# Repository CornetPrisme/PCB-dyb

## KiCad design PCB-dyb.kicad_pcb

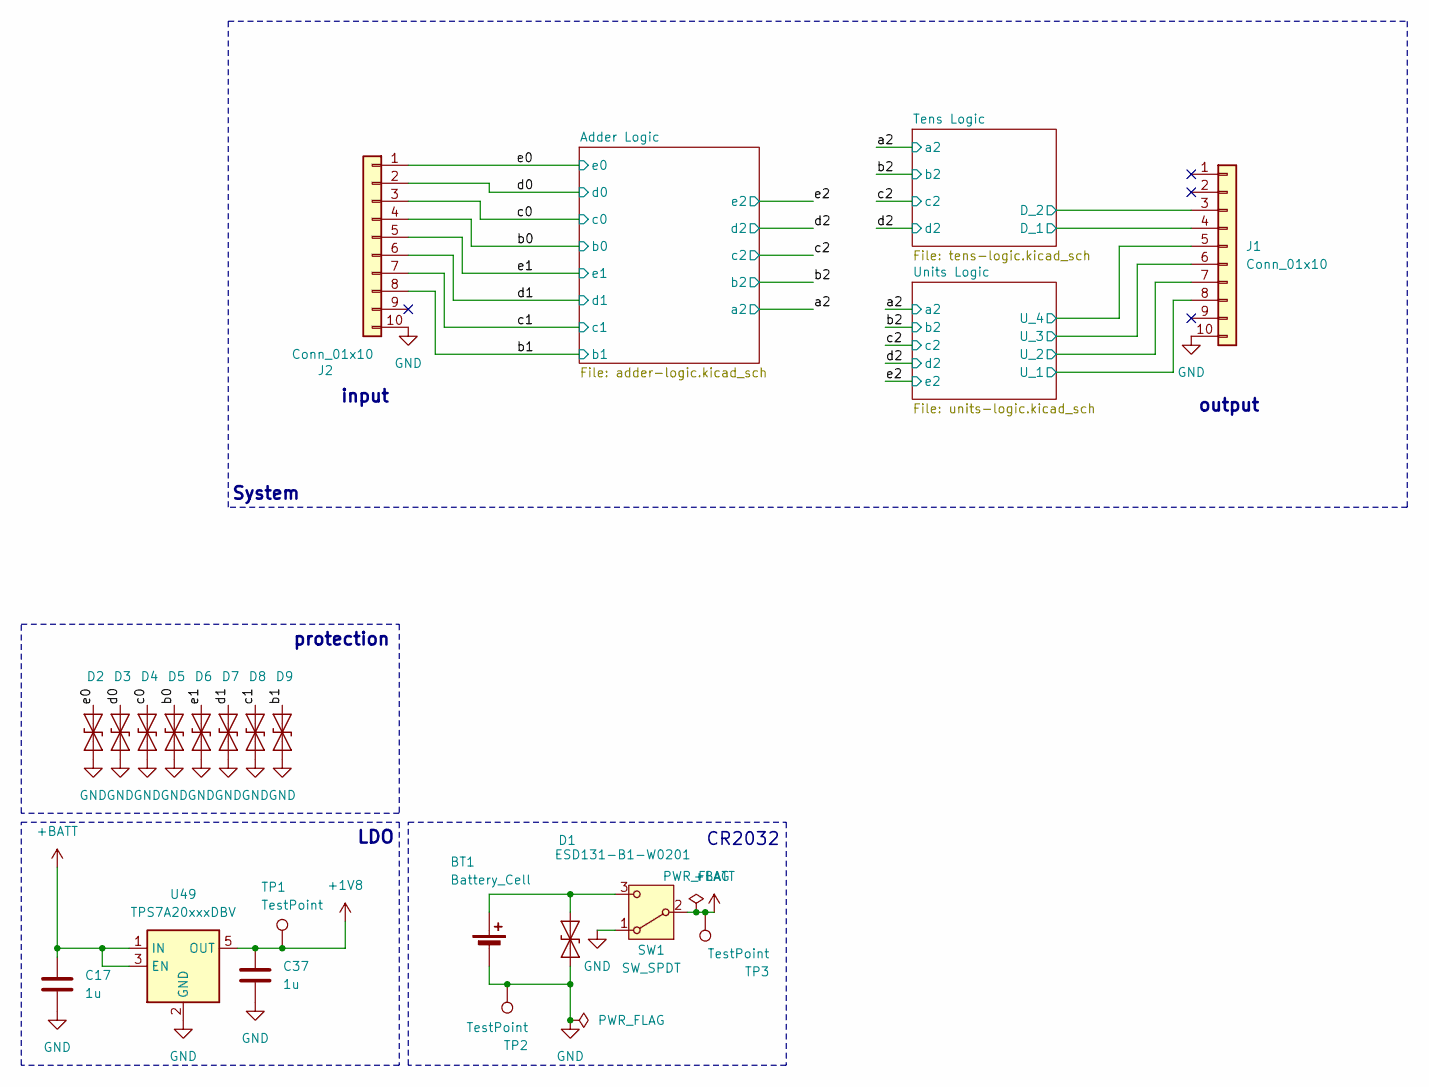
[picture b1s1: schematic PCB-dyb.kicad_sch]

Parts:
BT1: Battery_Cell; Manufacturer Part Number BS-08-B2AA016; JLCPCB Part # C964792
C17, C37: 1u; C_0603_1608Metric; Manufacturer Part Number CL10A105KO8NNNC; JLCPCB Part # C1592
D1, D2, D3, D4, D5, D6, D7, D8, D9: ESD131-B1-W0201; Infineon_SG-WLL-2-3_0.58x0.28_P0.36mm; Manufacturer Part Number TSD05CDYFR; JLCPCB Part # C20611048
J1, J2: Conn_01x10; PinHeader_1x10_P2.54mm_Vertical
SW1: SW_SPDT; SW_SPDT_Shouhan_MSK12C02; Manufacturer Part Number MSK12C02; JLCPCB Part # C431540
TP1, TP2, TP3: TestPoint
U49: TPS7A20xxxDBV; SOT-23-5; Manufacturer Part Number TPS7A2018PDBVR; JLCPCB Part # C963430

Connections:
+1V8: C37.1, TP1.1, U49.5 (OUT); also elsewhere on the board
+BATT: C17.1, SW1.2 (B), TP3.1, U49.1 (IN), U49.3 (EN)
/Tens Logic/D_1: J1.4; also elsewhere on the board
/Tens Logic/D_2: J1.3; also elsewhere on the board
/Units Logic/U_2: J1.7; also elsewhere on the board
/Units Logic/U_3: J1.6; also elsewhere on the board
/Units Logic/U_4: J1.5; also elsewhere on the board
/b0: D5.2 (A2), J2.4; also elsewhere on the board
/b1: D9.2 (A2), J2.8; also elsewhere on the board
/c0: D4.2 (A2), J2.3; also elsewhere on the board
/c1: D8.2 (A2), J2.7; also elsewhere on the board
/d0: D3.2 (A2), J2.2; also elsewhere on the board
/d1: D7.2 (A2), J2.6; also elsewhere on the board
/e0: D2.2 (A2), J2.1; also elsewhere on the board
/e1: D6.2 (A2), J2.5; also elsewhere on the board
/e2: J1.8; also elsewhere on the board
GND: BT1.2 (-), C17.2, C37.2, D1.1 (A1), D2.1 (A1), D3.1 (A1), D4.1 (A1), D5.1 (A1), D6.1 (A1), D7.1 (A1), D8.1 (A1), D9.1 (A1), J1.10, J2.10, SW1.1 (A), TP2.1, U49.2 (GND); also elsewhere on the board
unnamed: BT1.1 (+), D1.2 (A2), SW1.3 (C)

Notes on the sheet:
CR2032
System
output
protection
LDO
input

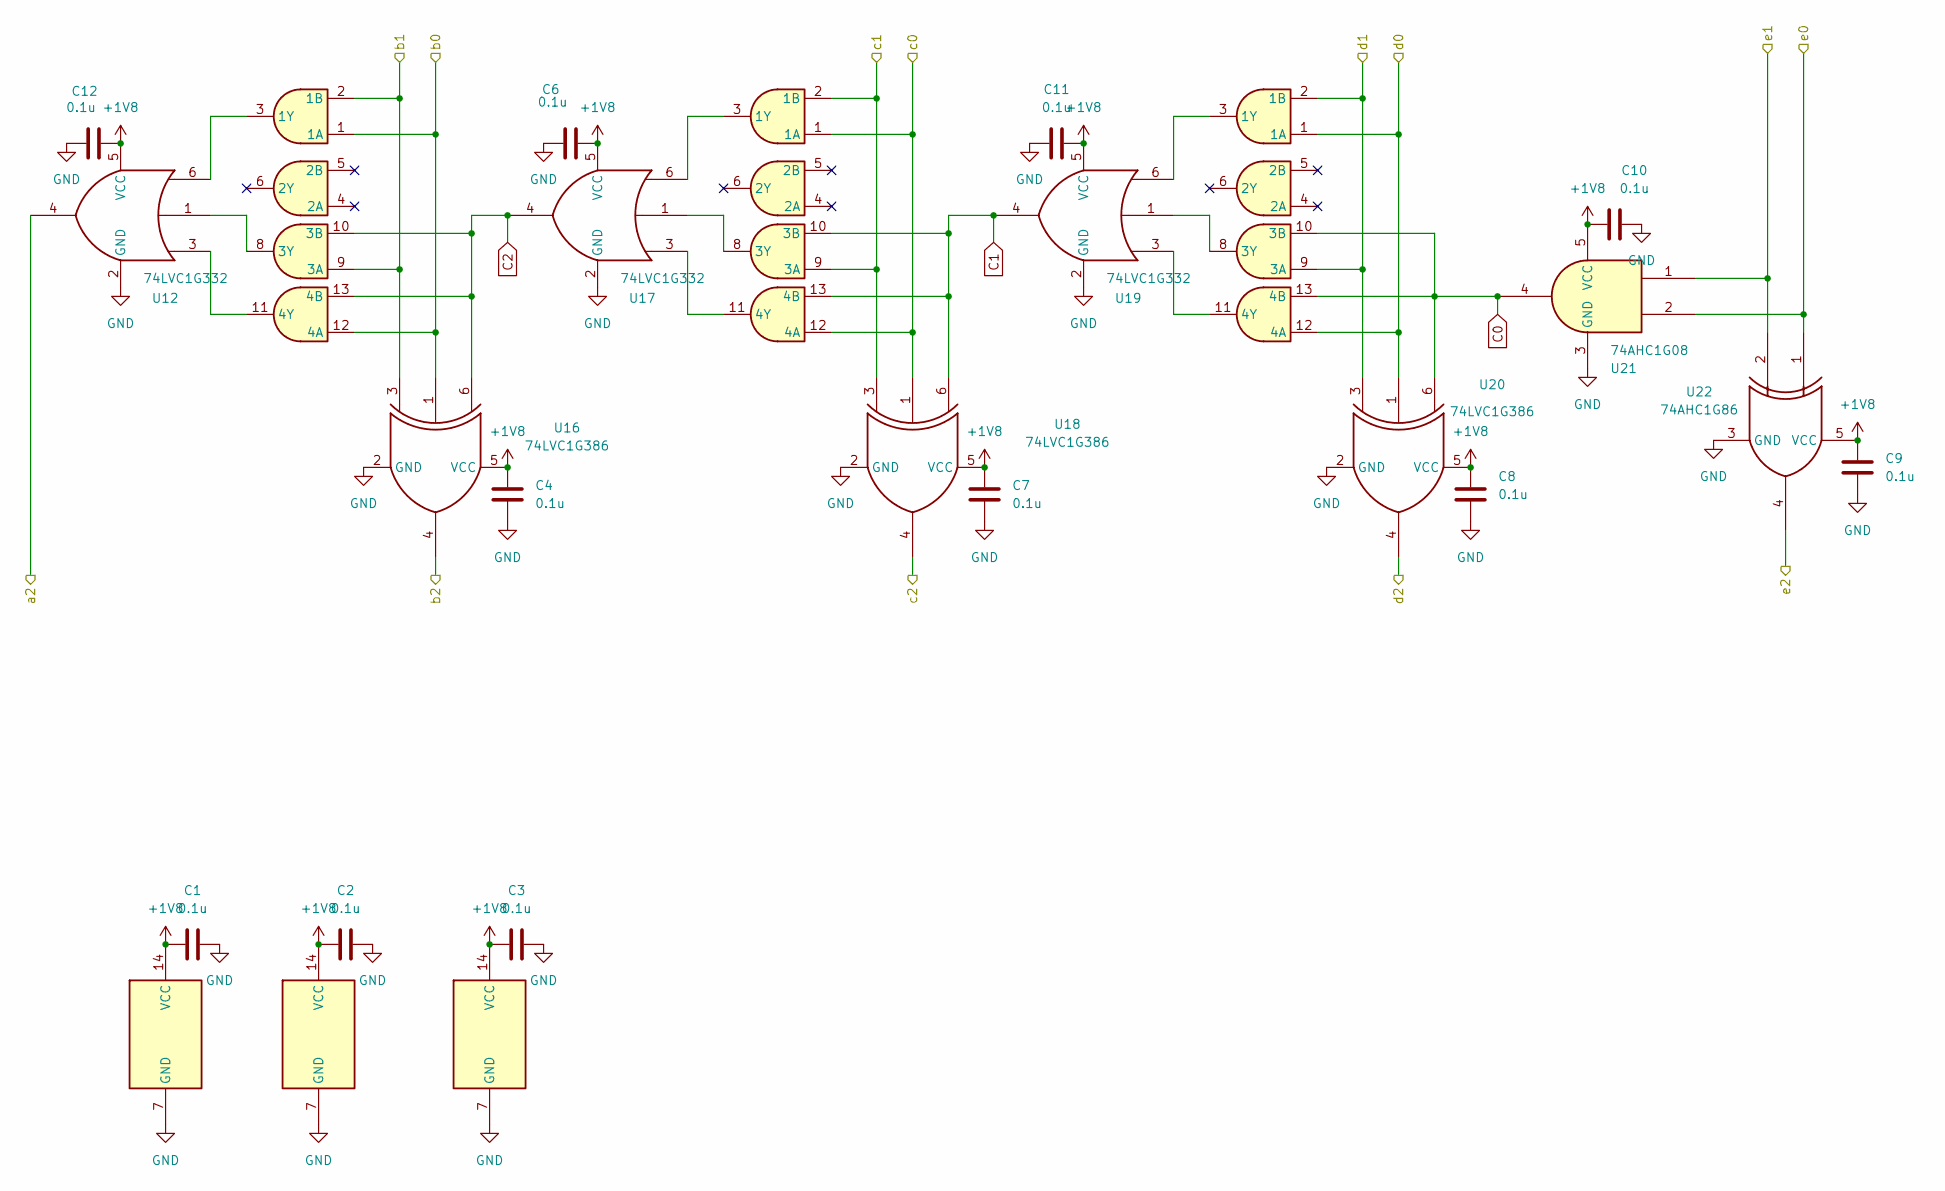
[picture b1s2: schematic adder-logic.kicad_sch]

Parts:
C1, C2, C3, C4, C6, C7, C8, C9, C10, C11, C12: 0.1u; C_0603_1608Metric; Manufacturer Part Number CL10B104KB8NNNC; JLCPCB Part # C1591
U12, U17, U19: 74LVC1G332; SOT-23-6; Manufacturer Part Number SN74LVC1G332DBVR; JLCPCB Part # C43368
U13, U14, U15: SOIC-14_3.9x8.7mm_P1.27mm; Manufacturer Part Number SN74ALVC08DR; JLCPCB Part # C2868761
U16, U18, U20: 74LVC1G386; Texas_R-PDSO-G6; Manufacturer Part Number SN74LVC1G386DCKR; JLCPCB Part # C2867271
U21: 74AHC1G08; SOT-353_SC-70-5; Manufacturer Part Number SN74AUC1G08DCKR; JLCPCB Part # C2863707
U22: 74AHC1G86; SOT-353_SC-70-5; Manufacturer Part Number SN74AUC1G86DCKR; JLCPCB Part # C2869047

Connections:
+1V8: C1.1, C2.1, C3.1, C4.2, C6.2, C7.1, C8.2, C9.2, C10.1, C11.1, C12.1, U12.5 (VCC), U13.14 (VCC), U14.14 (VCC), U15.14 (VCC), U16.5 (VCC), U17.5 (VCC), U18.5 (VCC), U19.5 (VCC), U20.5 (VCC), U21.5 (VCC), U22.5 (VCC); also elsewhere on the board
/a2: U12.4; also elsewhere on the board
/b0: U13.1 (1A), U13.12 (4A), U16.1; also elsewhere on the board
/b1: U13.2 (1B), U13.9 (3A), U16.3; also elsewhere on the board
/b2: U16.4; also elsewhere on the board
/c0: U14.1 (1A), U14.12 (4A), U18.1; also elsewhere on the board
/c1: U14.2 (1B), U14.9 (3A), U18.3; also elsewhere on the board
/c2: U18.4; also elsewhere on the board
/d0: U15.1 (1A), U15.12 (4A), U20.1; also elsewhere on the board
/d1: U15.2 (1B), U15.9 (3A), U20.3; also elsewhere on the board
/d2: U20.4; also elsewhere on the board
/e0: U21.2, U22.1; also elsewhere on the board
/e1: U21.1, U22.2; also elsewhere on the board
/e2: U22.4; also elsewhere on the board
C0: U15.10 (3B), U15.13 (4B), U20.6, U21.4
C1: U14.10 (3B), U14.13 (4B), U18.6, U19.4
C2: U13.10 (3B), U13.13 (4B), U16.6, U17.4
GND: C1.2, C2.2, C3.2, C4.1, C6.1, C7.2, C8.1, C9.1, C10.2, C11.2, C12.2, U12.2 (GND), U13.7 (GND), U14.7 (GND), U15.7 (GND), U16.2 (GND), U17.2 (GND), U18.2 (GND), U19.2 (GND), U20.2 (GND), U21.3 (GND), U22.3 (GND); also elsewhere on the board
unnamed: U12.6, U13.3 (1Y)
unnamed: U12.1, U13.8 (3Y)
unnamed: U12.3, U13.11 (4Y)
unnamed: U14.3 (1Y), U17.6
unnamed: U14.8 (3Y), U17.1
unnamed: U14.11 (4Y), U17.3
unnamed: U15.3 (1Y), U19.6
unnamed: U15.8 (3Y), U19.1
unnamed: U15.11 (4Y), U19.3

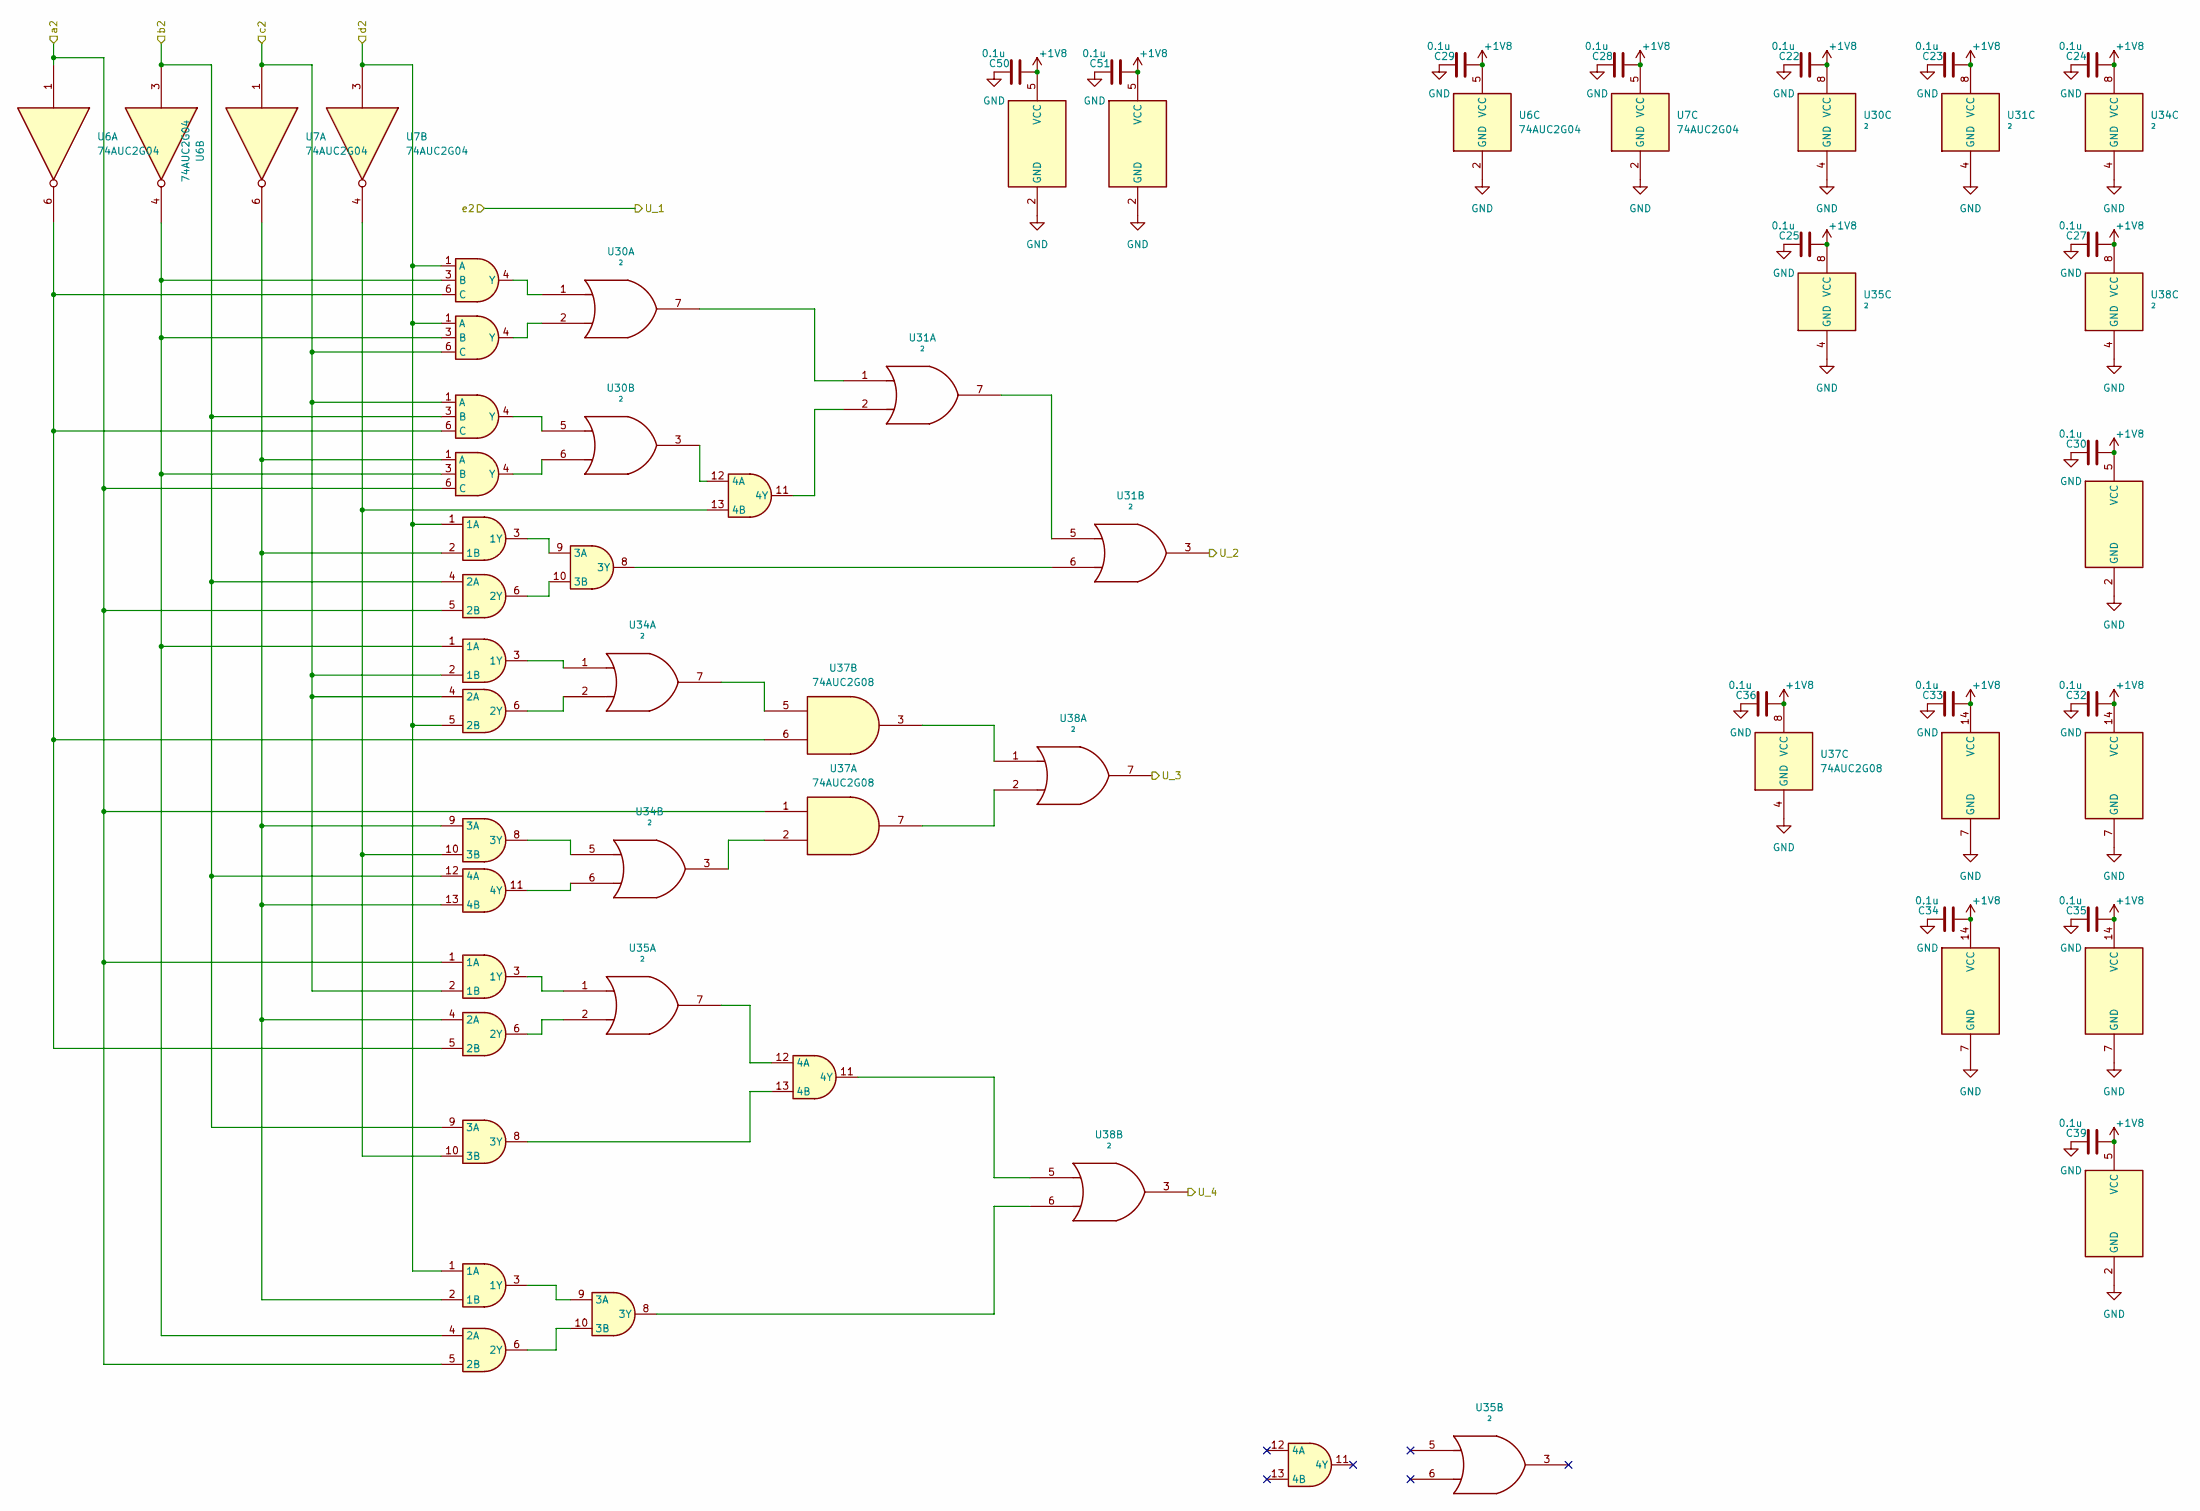
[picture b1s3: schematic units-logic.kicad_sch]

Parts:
C22, C23, C24, C25, C27, C28, C29, C30, C32, C33, C34, C35, C36, C39, C50, C51: 0.1u; C_0603_1608Metric; Manufacturer Part Number CL10B104KB8NNNC; JLCPCB Part # C1591
U6, U7: 74AUC2G04; Texas_R-PDSO-G6; Manufacturer Part Number SN74AUP2G14DCKR; JLCPCB Part # C139318
U9, U36, U39, U41: SOIC-14_3.9x8.7mm_P1.27mm; Manufacturer Part Number SN74ALVC08DR; JLCPCB Part # C2868761
U10, U11, U32, U33: SOT-23-6; Manufacturer Part Number SN74LVC1G11DBVR; JLCPCB Part # C22046
U30, U31, U34, U35, U38: ²; VSSOP-8_3x3mm_P0.65mm; Manufacturer Part Number SN74AUP2G32DCUR; JLCPCB Part # C2876519
U37: 74AUC2G08; Texas_DGN0008B_VSSOP-8-1EP_3x3mm_P0.65mm_EP2x3mm_Mask1.88x1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; Manufacturer Part Number SN74AUC2G08DCUR; JLCPCB Part # C2860154

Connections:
+1V8: C22.2, C23.2, C24.2, C25.2, C27.2, C28.2, C29.2, C30.2, C32.2, C33.2, C34.2, C35.2, C36.2, C39.2, C50.2, C51.2, U6.5 (VCC), U7.5 (VCC), U9.14 (VCC), U10.5 (VCC), U11.5 (VCC), U30.8 (VCC), U31.8 (VCC), U32.5 (VCC), U33.5 (VCC), U34.8 (VCC), U35.8 (VCC), U36.14 (VCC), U37.8 (VCC), U38.8 (VCC), U39.14 (VCC), U41.14 (VCC); also elsewhere on the board
/Units Logic/U_2: U31.3; also elsewhere on the board
/Units Logic/U_3: U38.7; also elsewhere on the board
/Units Logic/U_4: U38.3; also elsewhere on the board
/a2: U6.1, U9.5 (2B), U33.6 (C), U37.1, U39.1 (1A), U41.5 (2B); also elsewhere on the board
/b2: U6.3, U9.4 (2A), U32.3 (B), U36.12 (4A), U39.9 (3A); also elsewhere on the board
/c2: U7.1, U10.6 (C), U32.1 (A), U36.2 (1B), U36.4 (2A), U39.2 (1B); also elsewhere on the board
/d2: U7.3, U9.1 (1A), U10.1 (A), U11.1 (A), U36.5 (2B), U41.1 (1A); also elsewhere on the board
GND: C22.1, C23.1, C24.1, C25.1, C27.1, C28.1, C29.1, C30.1, C32.1, C33.1, C34.1, C35.1, C36.1, C39.1, C50.1, C51.1, U6.2 (GND), U7.2 (GND), U9.7 (GND), U10.2 (GND), U11.2 (GND), U30.4 (GND), U31.4 (GND), U32.2 (GND), U33.2 (GND), U34.4 (GND), U35.4 (GND), U36.7 (GND), U37.4 (GND), U38.4 (GND), U39.7 (GND), U41.7 (GND); also elsewhere on the board
unnamed: U9.3 (1Y), U9.9 (3A)
unnamed: U9.6 (2Y), U9.10 (3B)
unnamed: U9.8 (3Y), U31.6
unnamed: U9.12 (4A), U30.3
unnamed: U9.11 (4Y), U31.2
unnamed: U6.4, U10.3 (B), U11.3 (B), U33.3 (B), U36.1 (1A), U41.4 (2A)
unnamed: U10.4 (Y), U30.2
unnamed: U6.6, U11.6 (C), U32.6 (C), U37.6, U39.5 (2B)
unnamed: U11.4 (Y), U30.1
unnamed: U30.7, U31.1
unnamed: U31.5, U31.7
unnamed: U30.5, U32.4 (Y)
unnamed: U7.6, U9.2 (1B), U33.1 (A), U36.9 (3A), U36.13 (4B), U39.4 (2A), U41.2 (1B)
unnamed: U30.6, U33.4 (Y)
unnamed: U34.3, U37.2
unnamed: U34.7, U37.5
unnamed: U34.1, U36.3 (1Y)
unnamed: U34.2, U36.6 (2Y)
unnamed: U7.4, U9.13 (4B), U36.10 (3B), U39.10 (3B)
unnamed: U34.5, U36.8 (3Y)
unnamed: U34.6, U36.11 (4Y)
unnamed: U37.3, U38.1
unnamed: U37.7, U38.2
unnamed: U35.1, U39.3 (1Y)
unnamed: U35.2, U39.6 (2Y)
unnamed: U39.8 (3Y), U39.13 (4B)
unnamed: U35.7, U39.12 (4A)
unnamed: U38.5, U39.11 (4Y)
unnamed: U41.3 (1Y), U41.9 (3A)
unnamed: U41.6 (2Y), U41.10 (3B)
unnamed: U38.6, U41.8 (3Y)

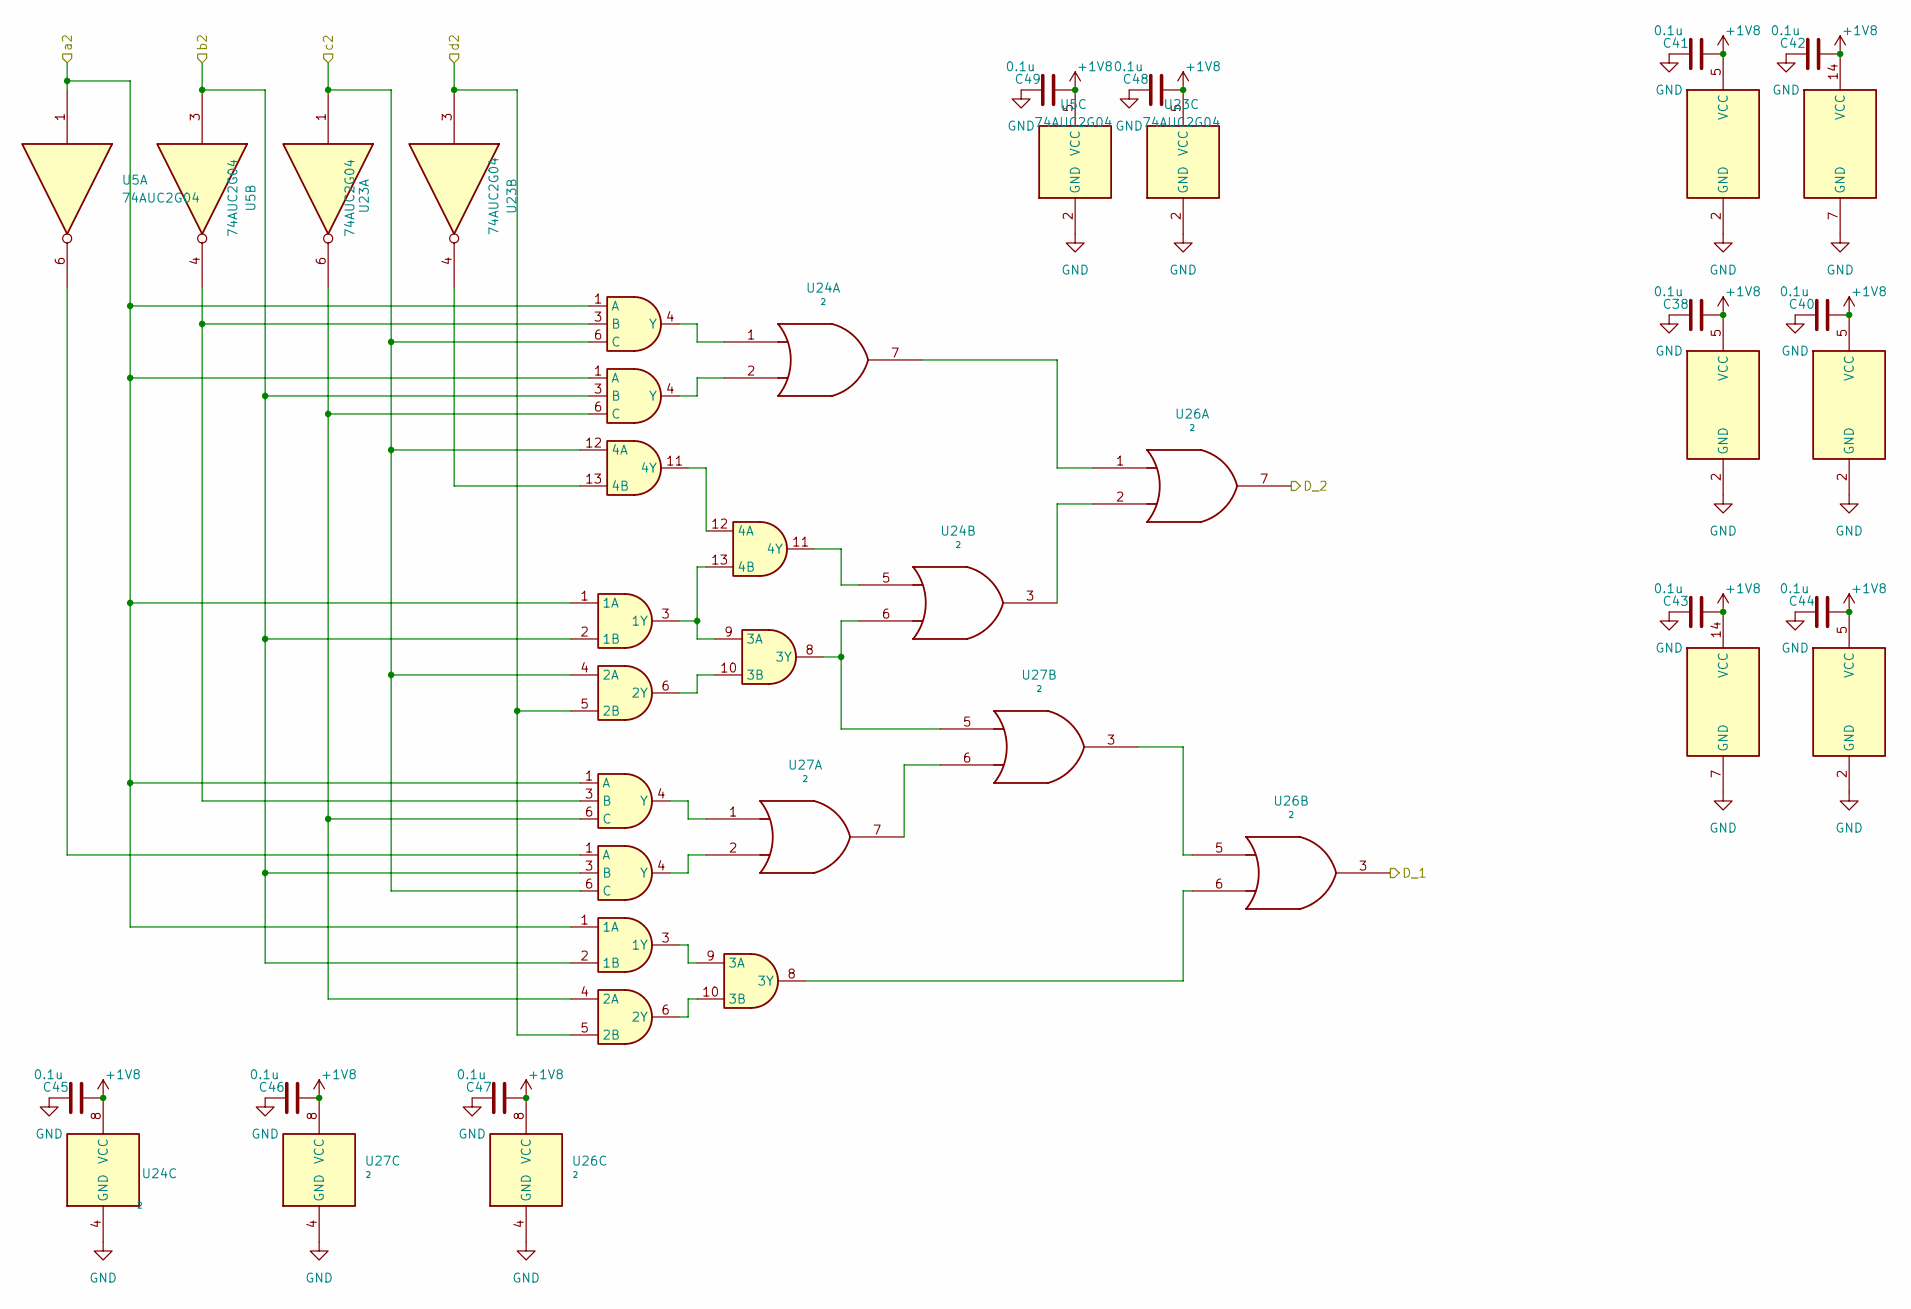
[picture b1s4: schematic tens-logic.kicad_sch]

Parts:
C38, C40, C41, C42, C43, C44, C45, C46, C47, C48, C49: 0.1u; C_0603_1608Metric; Manufacturer Part Number CL10B104KB8NNNC; JLCPCB Part # C1591
U1, U2, U3, U4: SOT-23-6; Manufacturer Part Number SN74LVC1G11DBVR; JLCPCB Part # C22046
U5, U23: 74AUC2G04; Texas_R-PDSO-G6; Manufacturer Part Number SN74AUP2G14DCKR; JLCPCB Part # C139318
U8, U25: SOIC-14_3.9x8.7mm_P1.27mm; Manufacturer Part Number SN74ALVC08DR; JLCPCB Part # C2868761
U24, U26, U27: ²; VSSOP-8_3x3mm_P0.65mm; Manufacturer Part Number SN74AUP2G32DCUR; JLCPCB Part # C2876519

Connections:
+1V8: C38.2, C40.2, C41.2, C42.2, C43.2, C44.2, C45.2, C46.2, C47.2, C48.2, C49.2, U1.5 (VCC), U2.5 (VCC), U3.5 (VCC), U4.5 (VCC), U5.5 (VCC), U8.14 (VCC), U23.5 (VCC), U24.8 (VCC), U25.14 (VCC), U26.8 (VCC), U27.8 (VCC); also elsewhere on the board
/Tens Logic/D_1: U26.3; also elsewhere on the board
/Tens Logic/D_2: U26.7; also elsewhere on the board
/a2: U1.1 (A), U2.1 (A), U3.1 (A), U5.1, U8.1 (1A), U25.1 (1A); also elsewhere on the board
/b2: U1.3 (B), U4.3 (B), U5.3, U8.2 (1B), U25.2 (1B); also elsewhere on the board
/c2: U2.6 (C), U4.6 (C), U23.1, U25.4 (2A), U25.12 (4A); also elsewhere on the board
/d2: U8.5 (2B), U23.3, U25.5 (2B); also elsewhere on the board
GND: C38.1, C40.1, C41.1, C42.1, C43.1, C44.1, C45.1, C46.1, C47.1, C48.1, C49.1, U1.2 (GND), U2.2 (GND), U3.2 (GND), U4.2 (GND), U5.2 (GND), U8.7 (GND), U23.2 (GND), U24.4 (GND), U25.7 (GND), U26.4 (GND), U27.4 (GND); also elsewhere on the board
unnamed: U1.6 (C), U3.6 (C), U8.4 (2A), U23.6
unnamed: U1.4 (Y), U24.2
unnamed: U2.3 (B), U3.3 (B), U5.4
unnamed: U2.4 (Y), U24.1
unnamed: U3.4 (Y), U27.1
unnamed: U4.1 (A), U5.6
unnamed: U4.4 (Y), U27.2
unnamed: U8.3 (1Y), U8.9 (3A)
unnamed: U8.6 (2Y), U8.10 (3B)
unnamed: U8.8 (3Y), U26.6
unnamed: U8.11 (4Y), U24.5
unnamed: U24.3, U26.2
unnamed: U24.7, U26.1
unnamed: U8.13 (4B), U25.3 (1Y), U25.9 (3A)
unnamed: U25.6 (2Y), U25.10 (3B)
unnamed: U24.6, U25.8 (3Y), U27.5
unnamed: U23.4, U25.13 (4B)
unnamed: U8.12 (4A), U25.11 (4Y)
unnamed: U26.5, U27.3
unnamed: U27.6, U27.7

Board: 2 copper layers, 91 parts (0 on the bottom side), 85 nets, no tracks yet.
